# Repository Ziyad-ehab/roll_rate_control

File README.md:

# roll_rate_control
A Arduino based roll control project to minimze the angular rates around the body x axis (roll) of a body to a specified rate using Gy-91 sensor and bluetooth module
PCB was designed and implemented for system testing and verification

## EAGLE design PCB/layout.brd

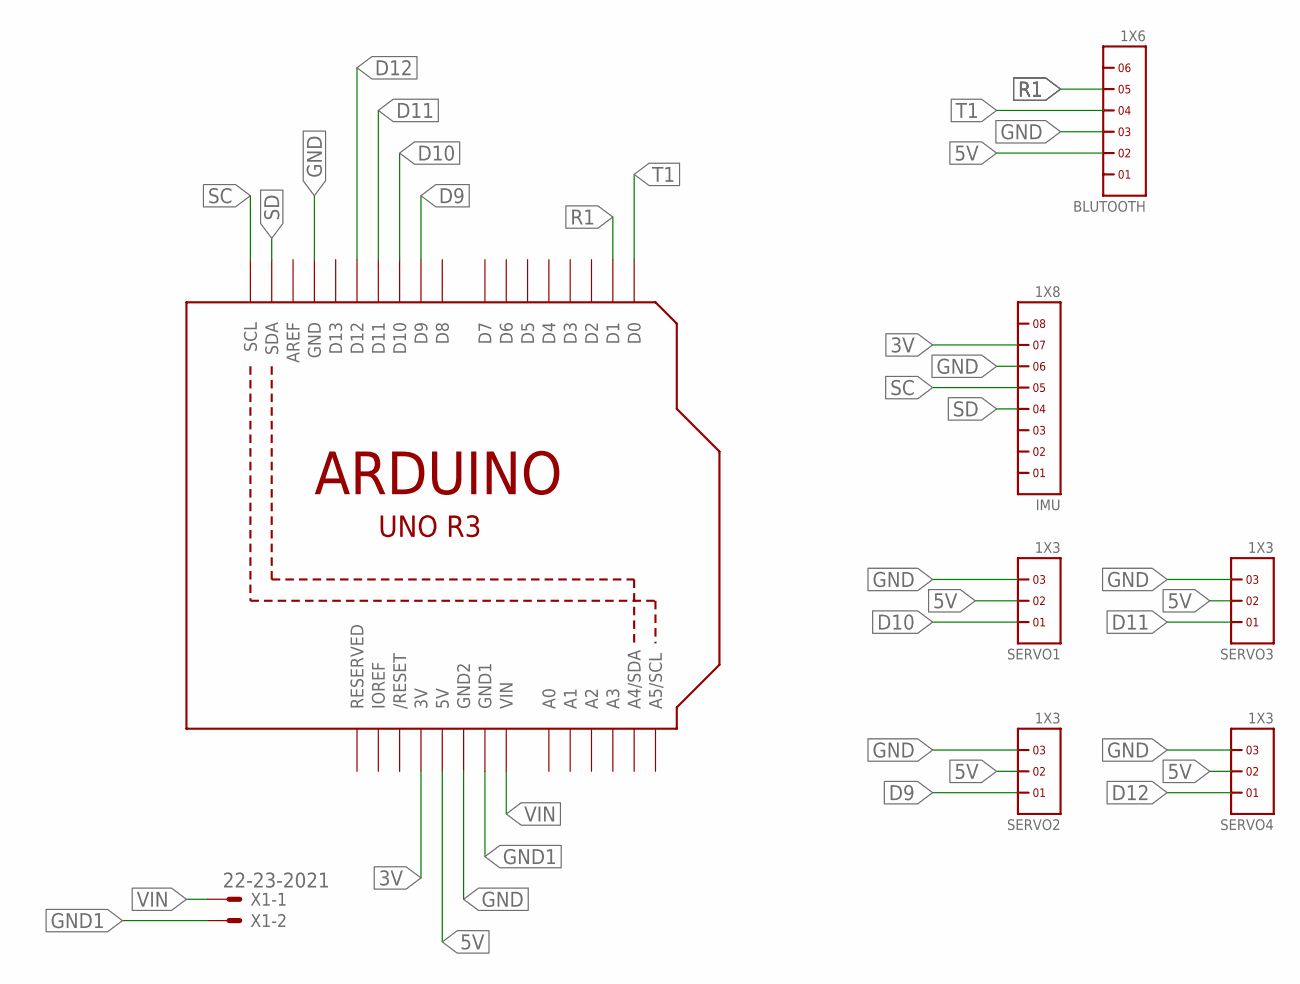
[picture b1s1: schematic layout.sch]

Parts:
BLUTOOTH: 1X6
IMU: 1X8
SERVO1, SERVO2, SERVO3, SERVO4: 1X3
U1: ARDUINOR3-DIMENSION; ARDUINOR3
X1: 22-23-2021

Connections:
3V: IMU.7, U1.3V
5V: BLUTOOTH.2, SERVO1.2, SERVO2.2, SERVO3.2, SERVO4.2, U1.5V
D9: SERVO2.1, U1.D9
D10: SERVO1.1, U1.D10
D11: SERVO3.1, U1.D11
D12: SERVO4.1, U1.D12
GND: BLUTOOTH.3, IMU.6, SERVO1.3, SERVO2.3, SERVO3.3, SERVO4.3, U1.GND, U1.GND2
GND1: U1.GND1, X1.2
R1: BLUTOOTH.5, U1.D1
SC: IMU.5, U1.SCL
SD: IMU.4, U1.SDA
T1: BLUTOOTH.4, U1.D0
VIN: U1.VIN, X1.1

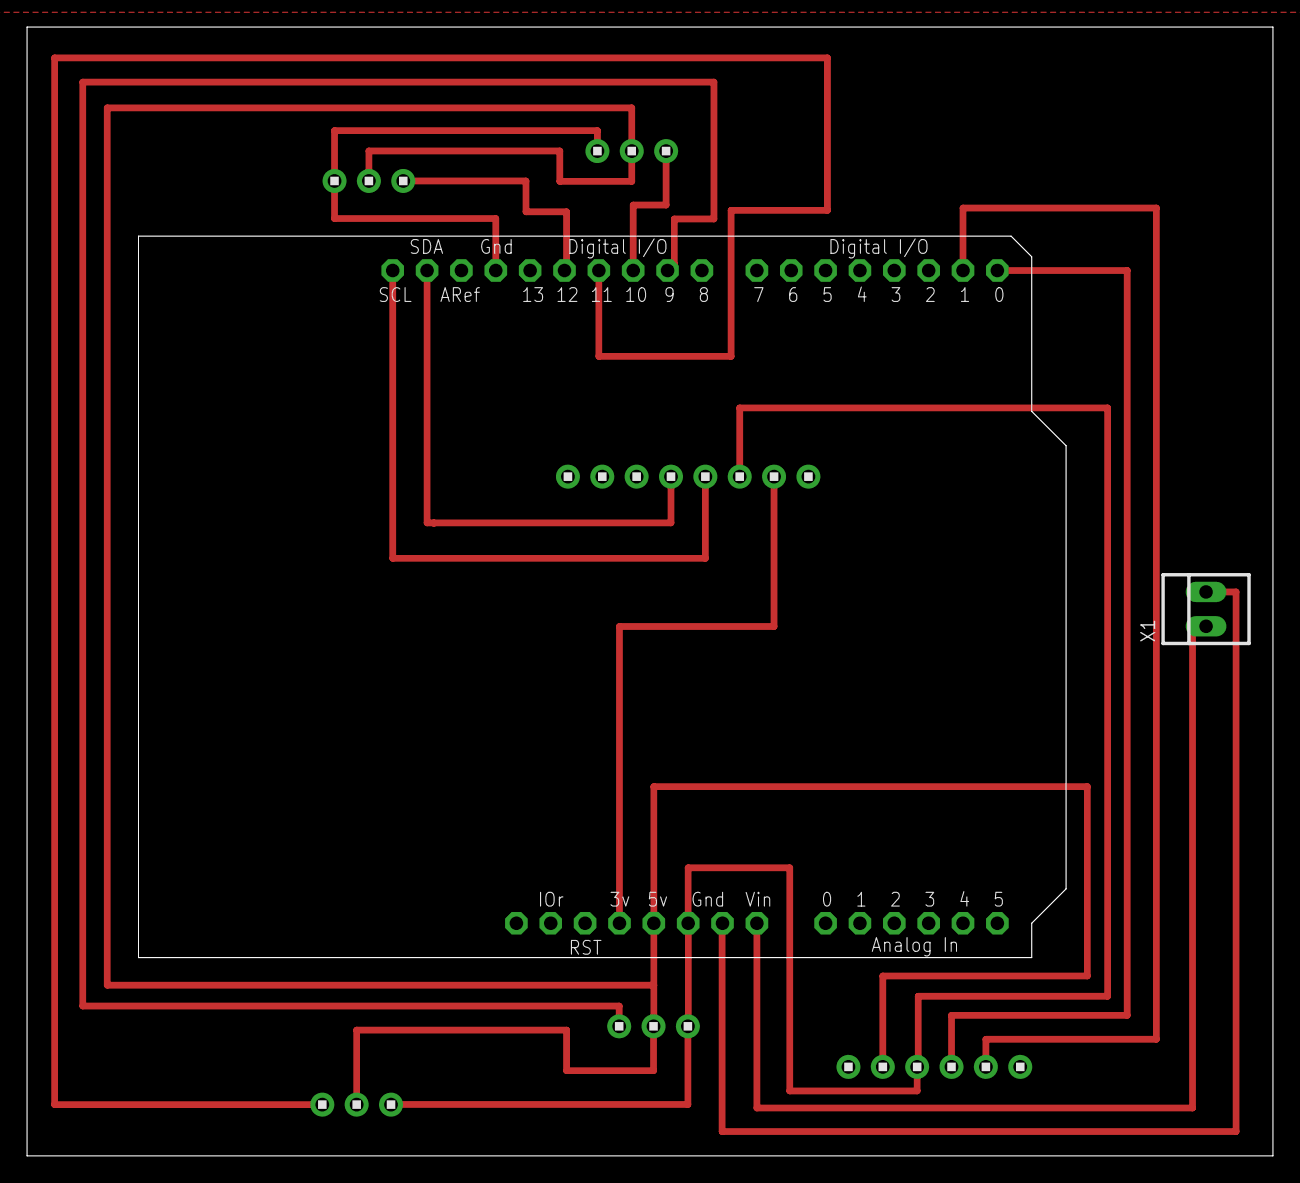
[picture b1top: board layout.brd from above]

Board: 2 copper layers, 92.1 x 83.5 mm, 8 parts (0 on the bottom side), 13 nets.

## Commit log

2024-11-11 README.md
